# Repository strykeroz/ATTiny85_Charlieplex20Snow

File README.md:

ATtiny85 "Snow" with 20 Charlieplexed LEDs
==========================================

ATtiny85 Xmas decorative effect, using Arduino core 

This project creates a falling snowflake effect (or rain?) as discussed in this Arduino forum thread: http://arduino.cc/forum/index.php/topic,135596.15.html

The animation has a bright LED at the head, and a tail of 4 others which fall at a slightly randomised speed, with a random delay between falls.  The animation slows during the fall, and the "snowflake" rests at the bottom while the tail collapses into it, before finally fading away.

Operation
---------
Animation operates while powered on.

ATtiny85 pin assignments 
------------------------
(legs numbered 1..8 counterclockwise from leg marked with dot)
 Leg  Function
 1    Reset, no connection
 2    D3 GREEN channel
 3    D4 ORANGE channel
 4    GND
 5    D0 WHITE channel
 6    D1 BLUE channel
 7    D2 YELLOW channel
 8    +5V

Code
----
Written using the Arduino IDE and Arduino-Tiny cores , the target to select is the ATtiny85 @ 8MHz (internal oscillator, BOD disabled).  Look up how to program the ATtiny using Arduino, and programming it using Arduino as an IDE.  

Tested installation
-------------------
For simplicity of wiring on breadboard, and for matching to function in the code, this was wired using a colour code.  A breadboard circuit diagram created in Fritzing is included to explain how two of those channels are wired.

I started the breadboard with a row of 20 LEDs, each with the flat side to the right.  For a more permanent installation, rotating the LEDs so the flat side is top or bottom would allow for ease of wiring.  Each group of 4 LEDs shares a direct connection to one pin directly without a resistor, with the 4 anodes (+, or the long LED leg) linked.  Then the other legs are connected via a current limiting resistor to the other colours in the sequence green, orange, white, blue, yellow (always in this order, but omitting of course the colour that the anodes are).

So the green group has green to the anodes, then the cathodes in left to right sequence are orange, white, blue & yellow.  The orange group has orange to the anodes, with green, white, blue & yellow to the cathodes left to right.  White group's cathodes are sequenced green, orange, blue & yellow; the blue group's cathodes go green, orange, white & yellow; and the yellow group's cathodes go green, orange, white & blue.

BoM as tested:
	1x ATtiny85-20PU
	1x 8 pin DIP IC Socket (optional, you might be confident soldering direct to the ATtiny to reduce weight)
	20x 5mm blue LED
	5x 100 Ohm resistors (current limiting, for LEDs)
	1x 0.1uF ceramic capacitor (decoupling)

Be sure to choose current limiting resistors to suit the particular LED you select.
  
Enjoy : )

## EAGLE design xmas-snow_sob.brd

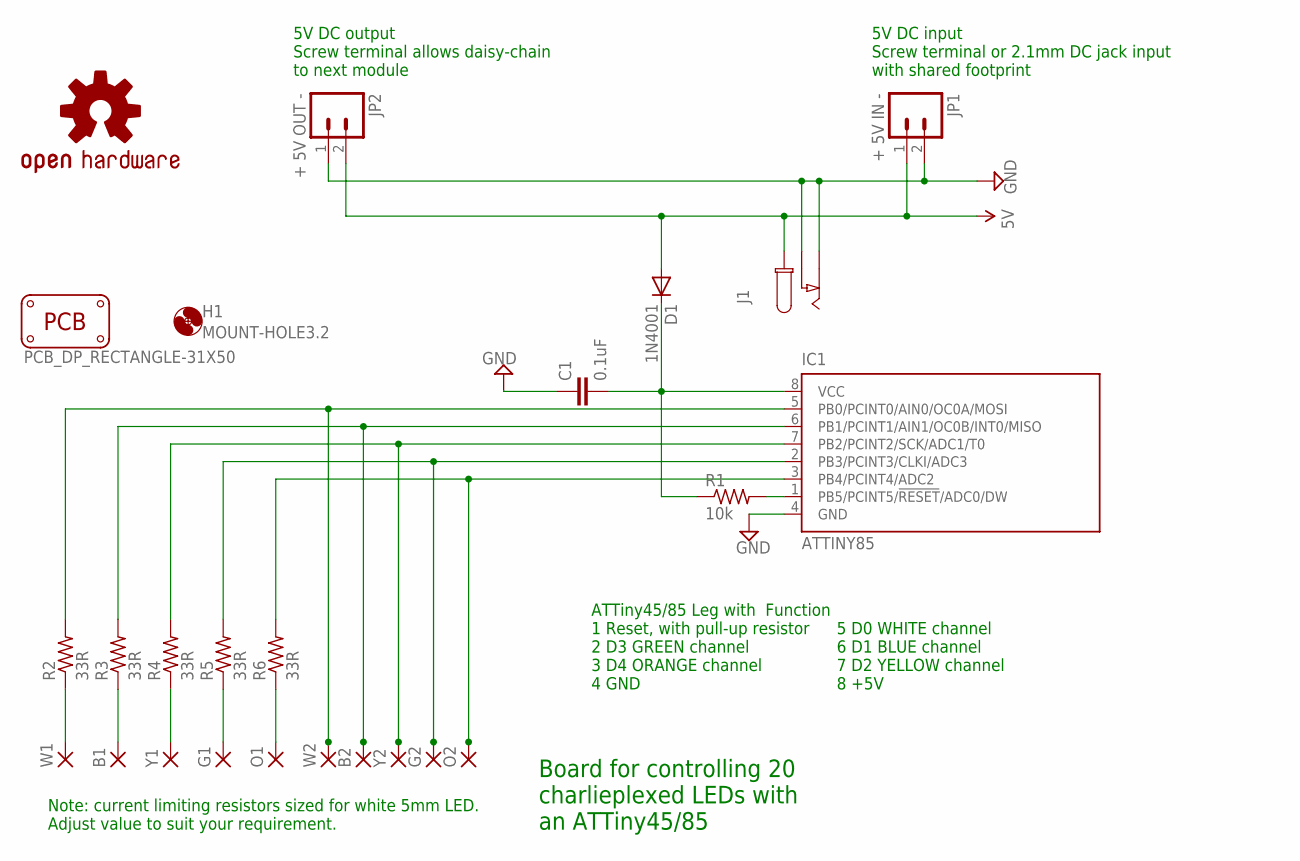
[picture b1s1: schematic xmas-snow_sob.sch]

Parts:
B1, B2: WIREPAD1,6/0,8; 1,6/0,8
C1: 0.1uF; CAP-PTH-SMALL2
D1: 1N4001; DO41-10
G1, G2: WIREPAD1,6/0,8; 1,6/0,8
H1: MOUNT-HOLE3.2; 3,2
IC1: ATTINY85; DIL08
J1: CON_DC_M-DC_PTH; DC_BARREL_JACK_PTH_2MM
JP1: + 5V IN -; SCREWTERMINAL-5MM-2
JP2: + 5V OUT -; SCREWTERMINAL-5MM-2
LOGO1: OSHW-LOGOL; OSHW-LOGO-L
O1, O2: WIREPAD1,6/0,8; 1,6/0,8
PCB1: PCB_DP_RECTANGLE-31X50; DP5031_V1
R1: 10k; 0207/2V
R2, R3, R4, R5, R6: 33R; 0207/2V
W1, W2: WIREPAD1,6/0,8; 1,6/0,8
Y1, Y2: WIREPAD1,6/0,8; 1,6/0,8

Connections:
5V: C1.2, D1.A, D1.C, IC1.8 (VCC), J1.P1, JP1.1, JP2.2, R1.1
GND: C1.1, IC1.4 (GND), J1.P2 (P3), J1.P3 (P2), JP1.2, JP2.1
unnamed: IC1.1 (PB5/PCINT5/!RESET!/ADC0/DW), R1.2
unnamed: IC1.5 (PB0/PCINT0/AIN0/OC0A/MOSI), R2.2, W2.1
unnamed: B2.1, IC1.6 (PB1/PCINT1/AIN1/OC0B/INT0/MISO), R3.2
unnamed: IC1.7 (PB2/PCINT2/SCK/ADC1/T0), R4.2, Y2.1
unnamed: G2.1, IC1.2 (PB3/PCINT3/CLKI/ADC3), R5.2
unnamed: IC1.3 (PB4/PCINT4/ADC2), O2.1, R6.2
unnamed: R2.1, W1.1
unnamed: B1.1, R3.1
unnamed: R4.1, Y1.1
unnamed: G1.1, R5.1
unnamed: O1.1, R6.1

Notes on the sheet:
ATTiny45/85 Leg with Function 1 Reset, with pull-up resistor 2 D3 GREEN channel 3 D4 ORANGE channel 4 GND
Board for controlling 20 charlieplexed LEDs with an ATTiny45/85
5V DC input Screw terminal or 2.1mm DC jack input with shared footprint
5V DC output Screw terminal allows daisy-chain to next module
5 D0 WHITE channel 6 D1 BLUE channel 7 D2 YELLOW channel 8 +5V
Note: current limiting resistors sized for white 5mm LED. Adjust value to suit your requirement.

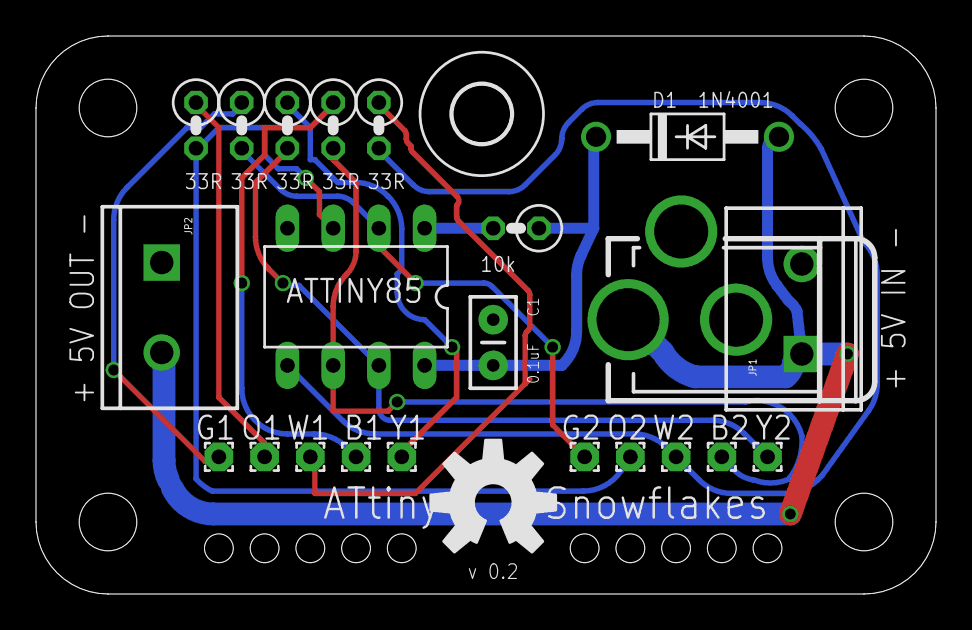
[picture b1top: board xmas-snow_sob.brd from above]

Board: 2 copper layers, 50.0 x 31.0 mm, 25 parts (0 on the bottom side), 13 nets.

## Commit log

2013-01-07 Initial
2013-01-07 added jpg of fritzing diagram
2013-01-07 added image
2013-10-26 Added EagleCAD files & Gerbers for Sick-of-Beige compatible PCB

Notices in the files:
parts and their libraries:
SparkFun-Passives: Licensing: CC v3.0 Share-Alike You are welcome to use this library for commercial purposes.
